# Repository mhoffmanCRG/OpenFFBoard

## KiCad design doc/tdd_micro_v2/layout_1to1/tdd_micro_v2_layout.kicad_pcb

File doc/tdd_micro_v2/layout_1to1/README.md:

# TDD Micro AASD-SERVO MMOS FFB v2.0: 1:1 layout (reconstructed)

Rebuilt on 2026-11-19 from the two CAM renders (top + bottom) and the OpenFFBoard F407VG_DISCO pin map.
This is reverse-engineered and unverified. It is not an official Thanos/tronicgr file.

## Files
| File | What it is |
|---|---|
| `tdd_micro_v2_layout.kicad_pcb` | KiCad 7 format (also opens in 8/9). Board outline, 30 footprints, 222 pads, 682 track segments, 56 vias, GND pours on both layers, and the silkscreen artwork vectorised 1:1 |
| `tdd_micro_v2_layout_1to1_A4.pdf` | Top and bottom at actual size on A4. Print at **100% / Actual size**, then check the 50 mm bar |
| `images/compare_*.png` | Original render (left) next to the recreation (right) |
| `tools/` | Python scripts that did the extraction (`make_pcb.py out`, then `render.py`, then `print_pdf.py x.pdf`) |

## Geometry (measured)
- Scale: 29.345 px/mm. Header pitch fits 2.54 mm (σ 0.04 px), DB25 fits 2.77 × 2.84 mm.
- Board: **79.35 × 80.95 mm**, square corners.
- Every hole matches its footprint pad within **0.10 mm**. Most are within 0.03 mm.
- Holes: headers 0.8/1.8 mm, DB9 0.8/1.75, DB25 1.05/1.65, LED 0.85/1.5, E-STOP 1.1 with 4.0×2.0 oval pads.
  Mounting holes: corners 3.5/6.0, DB9 shells 3.0/3.95, DB25 shell 3.15/3.75. Vias 0.3/0.7.
- Tracks are mostly 0.254 mm, with some at 0.4–0.8 mm. GND pour clearance is about 0.3 mm.

## After opening in KiCad
1. Press **B** to fill the GND zones. They are saved unfilled.
2. Run DRC and look at the ratsnest. Traces were vectorised automatically. Where silkscreen covered a trace (for example the big "THANOS" letters and the module header labels on the bottom), it may be broken or missing. Ratsnest lines show those gaps. Tracks without a net are fragments whose ends could not be resolved.
3. The DIY-MORE module is one footprint, **J1**, with three female headers. Pads are named `L1..L36` (left 2×18), `R1..R32` (right 2×16) and `B1..B24` (bottom 2×12). Each pad's *pin function* is its MCU pin (PE9, PA0, …).

The pad numbers do **not** match the symbols in `../tdd_micro_v2.kicad_sch`. Do not run "Update PCB from schematic".

## Connections confirmed from the copper
PE11→DB25-7 (DIR) · 5V→DB25-9 · PA2→DB25-15 (index) · PA1→DB25-20 · PB1→pedal GAS · PB0→BRAKE · PC5→Z header ·
PA4→shifter CS · PE0/PC10/PC11/PC7→button header · PD12→LED1 (green) anode · PD15→LED2 (blue) anode ·
DB25-25 (Vref)→torque-select jumper (PA4 pad) · U1 VCC↔C1 · U1 VOUTB↔left "B" jumper · U1 INA/INB↔right "A"/"B" jumpers ·
DB25 shell → "Shield Ground" jumper (bottom side) → GND.

## Differences from the earlier schematic (`../tdd_micro_v2.kicad_sch`)
- **E-STOP terminal**: pin 1 goes to **DB25-6 (SigIn1 / SON)** and pin 2 to GND. So the E-STOP switch enables the servo when closed. The schematic had "R4, EN source unknown". There is no R4 on the board.
- **AREF** on the SWD header is tied to **3V3**.
- **Encoder on DB25**: PA1 (ENC_B) is routed to **pin 20**, and the bottom silkscreen labels **pin 18 "ENC A"**. The schematic has these swapped.
- **DB25-1** looks unconnected. The schematic says GND.
- **U1 (LTC2644) pins 7–12**, from the chip silkscreen: 7 PD, 8 IN_B, 9 IN_A, 10 REF, 11 REFSEL, 12 GND. The schematic numbered these in the opposite order.
- The **solder jumpers are 2-pad**, not 3-pad. There are seven on top plus "Shield Ground" on the bottom:
  - right A/B connect DIR/PWM to DAC IN_A/IN_B;
  - left A/B pick VOUTA or VOUTB;
  - PA5 / PA4 / DAC pick what drives DB25-25 (Vref).

  The left-jumper and PA5/DAC connections are inferred from the layout, not proven by the copper.
- **LEDs** run MCU pin → LED anode → LED cathode → 470 Ω → GND, so the resistor is on the low side. Each LED footprint has both 3 mm THT pads and 1206 SMD pads.
- **"SPI2 pads (J9)"** are not a separate part. They are the module's bottom-header pins, labelled on the bottom silkscreen.
- The two **BOOT** pins on the left header are tied together.

## Still open
- **U1 IDLSEL (pin 4)**: the chip's silkscreen outline lies exactly on the pad ends, so I couldn't tell whether it ties to the GND pour. Measure it on the real board.
- The C1/C2/C3 GND sides, REFSEL and DB9 shell grounding come from the schematic, not the copper.

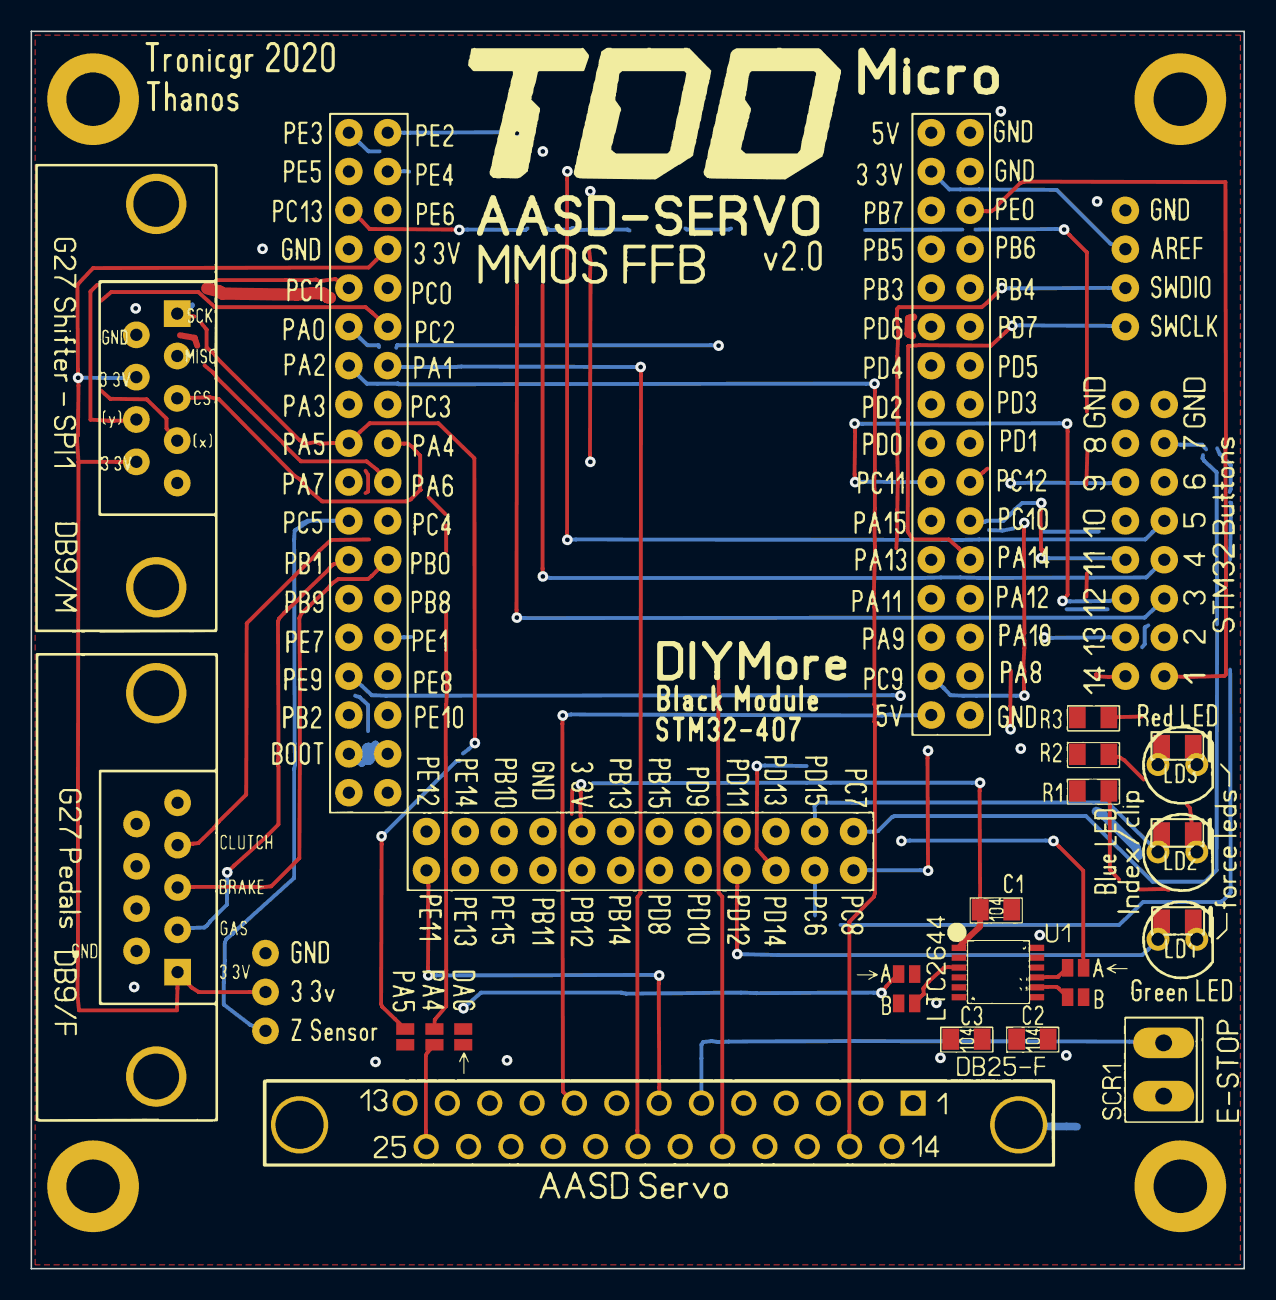
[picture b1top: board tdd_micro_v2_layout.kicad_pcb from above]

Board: 2 copper layers, 79.3 x 80.9 mm, 30 parts (1 on the bottom side), 48 nets.

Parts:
C1, C2, C3: 100nF; R_C_0805_HandSolder
D1: LED Green; LED_3mm_THT_plus_1206
D2: LED Blue; LED_3mm_THT_plus_1206
D3: LED Red; LED_3mm_THT_plus_1206
H1, H2, H3, H4: MountingHole 3.5mm; MountingHole_3.5mm_Pad
J1: DIY-MORE STM32F407VGT6 black module; DIYMORE_F407_Black_Sockets
J2: DB25 female -> AASD-30A CN2; DB25_Female_RA
J3: G27 Pedals (DB9 female); DB9_Female_RA
J4: G27 Shifter (DB9 male, SPI1); DB9_Male_RA
J5: Z sensor; PinHeader_1x03_P2.54
J6: SWD/AREF; PinHeader_1x04_P2.54
J7: STM32 Buttons 1-14; PinHeader_2x08_P2.54
J8: E-STOP terminal (SCR1); TerminalBlock_1x02_P3.50
JP1: Jumper A (left); SolderJumper_2_Open
JP2: Jumper B (left); SolderJumper_2_Open
JP3: Jumper A (right); SolderJumper_2_Open
JP4: Jumper B (right); SolderJumper_2_Open
JP5: Torque src PA5; SolderJumper_2_Open_V
JP6: Torque src PA4; SolderJumper_2_Open_V
JP7: Torque src DAC; SolderJumper_2_Open_V
JP8: Shield Ground; SolderJumper_2_Open_Bottom
R1, R2, R3: 470R; R_C_0805_HandSolder
U1: LTC2644-L12; MSOP-12_Long_Pads

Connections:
+3V3: C1.1, C2.1, J1.B9 (3V3), J1.L8 (3V3), J1.R3 (3V3), J3.1 (3V3), J4.7 (3V3), J4.9 (3V3), J5.2 (3V3), J6.2 (AREF), U1.1 (VCC), U1.5 (IOVCC), U1.7 (PD)
+5V: J1.R1 (5V), J1.R31 (5V), J2.9
BOOT: J1.L33 (BOOT), J1.L34 (BOOT)
BRAKE: J1.L24 (PB0), J3.3 (BRAKE)
BTN1: J1.R6 (PE0), J7.16 (B1)
BTN2: J1.L28 (PE1), J7.14 (B2)
BTN3: J1.L2 (PE2), J7.12 (B3)
BTN4: J1.L1 (PE3), J7.10 (B4)
BTN5: J1.L4 (PE4), J7.8 (B5)
BTN6: J1.L3 (PE5), J7.6 (B6)
BTN7: J1.B22 (PC6), J7.4 (B7)
BTN8: J1.B23 (PC7), J7.3 (B8)
BTN9: J1.B24 (PC8), J7.5 (B9)
BTN10: J1.R29 (PC9), J7.7 (B10)
BTN11: J1.R22 (PC10), J7.9 (B11)
BTN12: J1.R19 (PC11), J7.11 (B12)
BTN13: J1.R20 (PC12), J7.13 (B13)
BTN14: J1.L5 (PC13), J7.15 (B14)
CLUTCH: J1.L22 (PC4), J3.4 (CLUTCH)
DAC_INA: JP3.1, U1.9 (INA)
DAC_INB: JP4.1, U1.8 (INB)
DAC_OUTA: JP1.2, U1.2 (VOUTA)
DAC_OUTB: JP2.2, U1.3 (VOUTB)
DAC_REF: C3.1, U1.10 (REF)
DAC_SEL: JP1.1, JP2.1, JP7.1
DIR: J1.B2 (PE11), J2.7, JP3.2
ENC_A: J1.L11 (PA0), J2.18
ENC_B: J1.L14 (PA1), J2.20
ENC_I: J1.L13 (PA2), J2.15
GAS: J1.L23 (PB1), J3.2 (GAS)
GND: C1.2, C2.2, C3.2, J1.B7 (GND), J1.L7 (GND), J1.R2 (GND), J1.R4 (GND), J1.R32 (GND), J2.10, J2.13, J3.6 (GND), J4.6 (GND), J5.1 (GND), J6.1 (GND), J7.1 (GND), J7.2 (GND), J8.2, JP8.2, R1.1, R2.1, R3.1, U1.6 (GND), U1.12 (GND)
LED_B: D2.1, J1.B21 (PD15)
LED_B_K: D2.2, R2.2
LED_G: D1.1, J1.B18 (PD12)
LED_G_K: D1.2, R1.2
LED_R: D3.1, J1.B20 (PD14)
LED_R_K: D3.2, R3.2
PA4_SPI1_CS: J1.L18 (PA4), J4.3 (CS), JP6.1
PA5_SPI1_SCK: J1.L17 (PA5), J4.1 (SCK), JP5.1
PWM: J1.L29 (PE9), JP4.2
SHIFT_X: J1.L12 (PC2), J4.4 (X)
SHIFT_Y: J1.L9 (PC1), J4.8 (Y)
SON_ESTOP: J2.6, J8.1
SPI1_MISO: J1.L20 (PA6), J4.2 (MISO)
SWCLK: J1.R24 (PA14), J6.4 (SWCLK)
SWDIO: J1.R23 (PA13), J6.3 (SWDIO)
TORQUE: J2.25, JP5.2, JP6.2, JP7.2
Z_SENSOR: J1.L21 (PC5), J5.3 (Z)

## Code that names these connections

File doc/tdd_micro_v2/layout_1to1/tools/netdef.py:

# Net assignment: copper-verified where possible, otherwise the reconstructed schematic + firmware
import fp
# MCU pin -> functional net name (F407VG_DISCO firmware + board silkscreen)
MCU={'PE9':'PWM','PE11':'DIR','PA0':'ENC_A','PA1':'ENC_B','PA2':'ENC_I','PA4':'PA4_SPI1_CS','PA5':'PA5_SPI1_SCK',
     'PA6':'SPI1_MISO','PA7':'SPI1_MOSI','PB12':'SPI2_CS','PB13':'SPI2_SCK','PB14':'SPI2_MISO','PB15':'SPI2_MOSI',
     'PB1':'GAS','PB0':'BRAKE','PC4':'CLUTCH','PC5':'Z_SENSOR','PC2':'SHIFT_X','PC1':'SHIFT_Y',
     'PD12':'LED_G','PD14':'LED_R','PD15':'LED_B','PA13':'SWDIO','PA14':'SWCLK',
     'PE0':'BTN1','PE1':'BTN2','PE2':'BTN3','PE3':'BTN4','PE4':'BTN5','PE5':'BTN6','PC6':'BTN7','PC7':'BTN8',
     'PC8':'BTN9','PC9':'BTN10','PC10':'BTN11','PC11':'BTN12','PC12':'BTN13','PC13':'BTN14',
     'GND':'GND','3V3':'+3V3','5V':'+5V','BOOT':'BOOT'}
def assign():
    N={}
    for f,p in fp.all_pads():
        r,n,nm=f['ref'],p['num'],p.get('name','')
        k=(r,n)
        if n=='MH' and r!='J2': N[k]=''; continue
        if r=='J1': N[k]=MCU.get(nm,'')
        elif r=='J6': N[k]={'GND':'GND','AREF':'+3V3','SWDIO':'SWDIO','SWCLK':'SWCLK'}[nm]
        elif r=='J7': N[k]='GND' if nm=='GND' else 'BTN'+nm[1:]
        elif r=='J5': N[k]={'GND':'GND','3V3':'+3V3','Z':'Z_SENSOR'}[nm]
        elif r=='J4': N[k]={'SCK':'PA5_SPI1_SCK','MISO':'SPI1_MISO','CS':'PA4_SPI1_CS','X':'SHIFT_X','Y':'SHIFT_Y','3V3':'+3V3','GND':'GND','NC':''}[nm]
        elif r=='J3': N[k]={'3V3':'+3V3','GAS':'GAS','BRAKE':'BRAKE','CLUTCH':'CLUTCH','GND':'GND','NC':''}[nm]
        elif r=='J2':
            N[k]={'6':'SON_ESTOP','7':'DIR','9':'+5V','10':'GND','13':'GND','15':'ENC_I','18':'ENC_A','20':'ENC_B','25':'TORQUE','MH':'SHIELD'}.get(n,'')
        elif r=='J8': N[k]={'1':'SON_ESTOP','2':'GND'}[n]
        elif r in ('D1','D2','D3'):
            col={'D1':'G','D2':'B','D3':'R'}[r]
            N[k]=f'LED_{col}' if n=='1' else f'LED_{col}_K'
        elif r in ('R1','R2','R3'):
            col={'R1':'G','R2':'B','R3':'R'}[r]
            N[k]='GND' if n=='1' else f'LED_{col}_K'
        elif r=='C1': N[k]='+3V3' if n=='1' else 'GND'
        elif r=='C2': N[k]='+3V3' if n=='1' else 'GND'
        elif r=='C3': N[k]='DAC_REF' if n=='1' else 'GND'
        elif r=='U1':
            N[k]={'VCC':'+3V3','IOVCC':'+3V3','PD':'+3V3','IDLSEL':'IDLSEL','REFSEL':'REFSEL','INA':'DAC_INA','INB':'DAC_INB',
                  'VOUTA':'DAC_OUTA','VOUTB':'DAC_OUTB','REF':'DAC_REF','GND':'GND'}[nm]
        elif r=='JP1': N[k]='DAC_SEL' if n=='1' else 'DAC_OUTA'
        elif r=='JP2': N[k]='DAC_SEL' if n=='1' else 'DAC_OUTB'
        elif r=='JP3': N[k]='DAC_INA' if n=='1' else 'DIR'
        elif r=='JP4': N[k]='DAC_INB' if n=='1' else 'PWM'
        elif r=='JP5': N[k]='PA5_SPI1_SCK' if n=='1' else 'TORQUE'
        elif r=='JP6': N[k]='PA4_SPI1_CS' if n=='1' else 'TORQUE'
        elif r=='JP7': N[k]='DAC_SEL' if n=='1' else 'TORQUE'
        elif r=='JP8': N[k]='SHIELD' if n=='1' else 'GND'
        else: N[k]=''
    return N
